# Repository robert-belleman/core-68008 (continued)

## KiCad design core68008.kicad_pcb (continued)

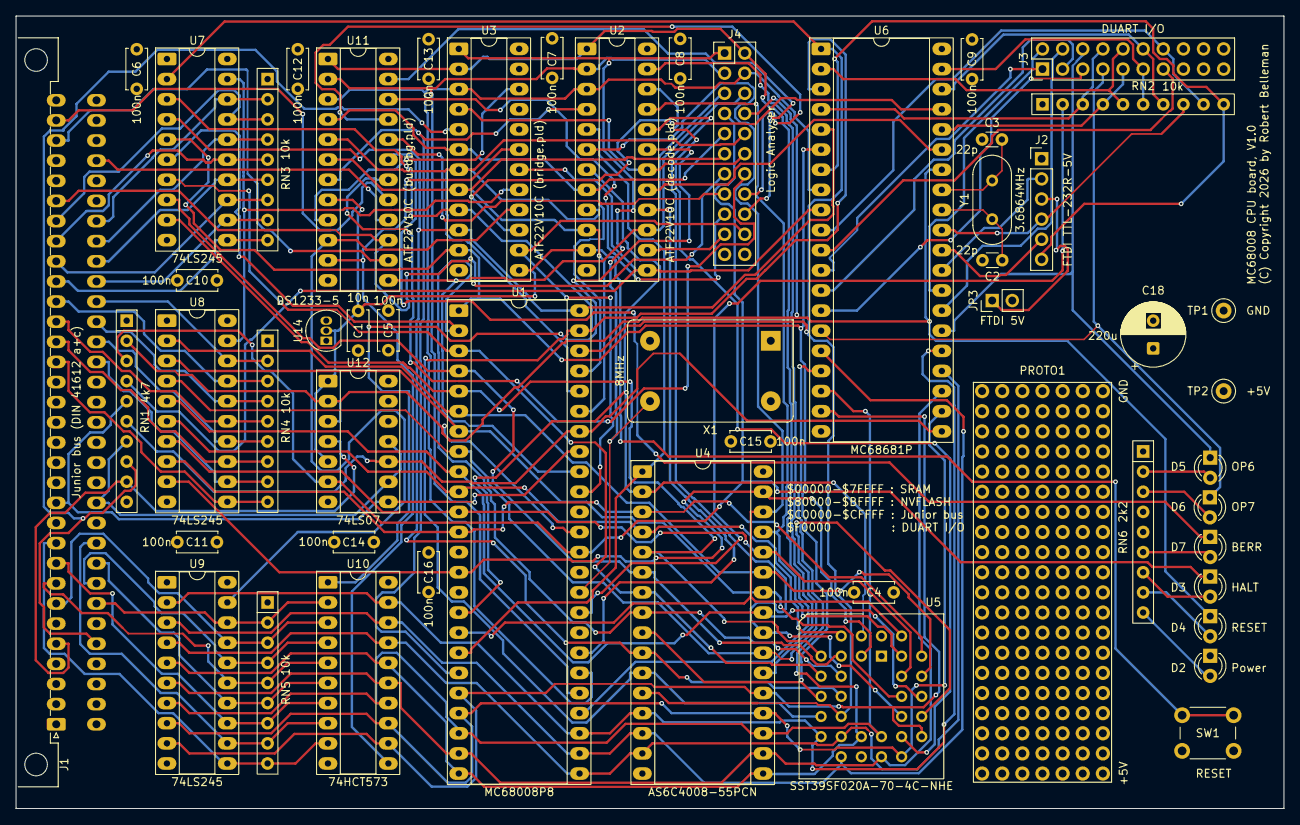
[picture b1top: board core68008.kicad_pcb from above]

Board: 4 copper layers, 160.0 x 100.0 mm, 53 parts (0 on the bottom side), 124 nets.

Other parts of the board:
PROTO1: Prototyping area; Proto_7x20_P2.54mm

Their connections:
+5V: PROTO1.134, PROTO1.135, PROTO1.136, PROTO1.137, PROTO1.138, PROTO1.139, PROTO1.140; also elsewhere on the board
GND: PROTO1.1, PROTO1.2, PROTO1.3, PROTO1.4, PROTO1.5, PROTO1.6, PROTO1.7; also elsewhere on the board
